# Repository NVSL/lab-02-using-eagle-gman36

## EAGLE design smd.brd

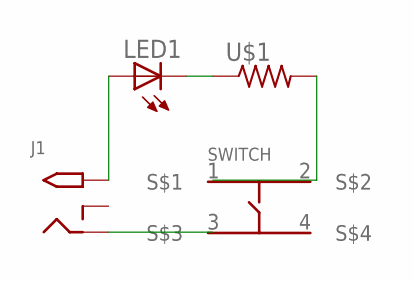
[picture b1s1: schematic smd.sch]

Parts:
J1: 2.1MMJACKTHM; PJ-102A
LED1: LED5MM
S1: 1301.9315
U$1: RESISTORTH-1/4W-CARBON; RESAD1160W55L680D260_HS

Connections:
unnamed: J1.TIP, LED1.A
unnamed: LED1.K (C), U$1.1

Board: 2 copper layers, 5 parts (0 on the bottom side), 2 nets, no tracks yet.

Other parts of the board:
U$3: UCSD_LOGO_LARGE

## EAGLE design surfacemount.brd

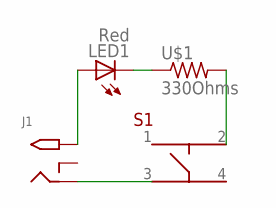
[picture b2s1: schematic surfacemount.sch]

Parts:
J1: 2.1MMJACKTHM; PJ-102A
LED1: Red; LED5MM
S1: 1301.9315
U$1: 330Ohms; RESAD1160W55L680D260_HS

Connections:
unnamed: J1.TIP, LED1.A
unnamed: LED1.K (C), U$1.1
unnamed: S1.2, U$1.2
unnamed: J1.RING, S1.3

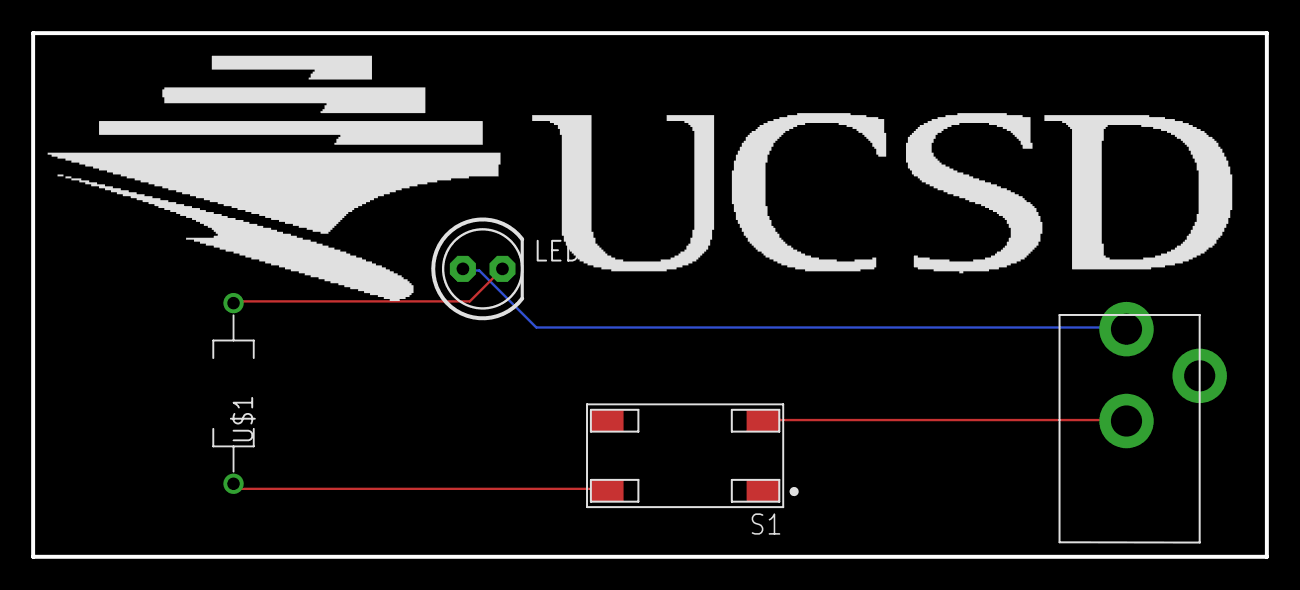
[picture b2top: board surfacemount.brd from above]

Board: 2 copper layers, 79.2 x 33.6 mm, 5 parts (0 on the bottom side), 4 nets.

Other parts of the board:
U$3: UCSD_LOGO_LARGE

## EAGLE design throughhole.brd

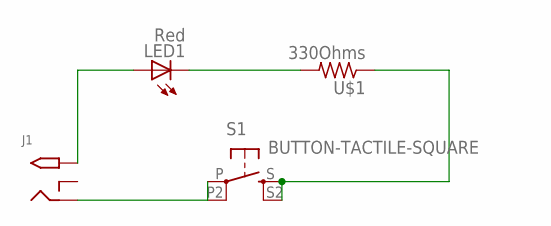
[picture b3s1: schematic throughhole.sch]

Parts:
J1: 2.1MMJACKTHM; PJ-102A
LED1: Red; LED5MM
S1: BUTTON-TACTILE-SQUARE; BUTTON-TACTILE-SQUARE-ADAFRUIT1010
U$1: 330Ohms; RESAD1160W55L680D260_HS

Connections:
unnamed: S1.S, S1.S2 (S1), U$1.1
unnamed: J1.RING, S1.P, S1.P2 (P1)
unnamed: J1.TIP, LED1.A
unnamed: LED1.K (C), U$1.2

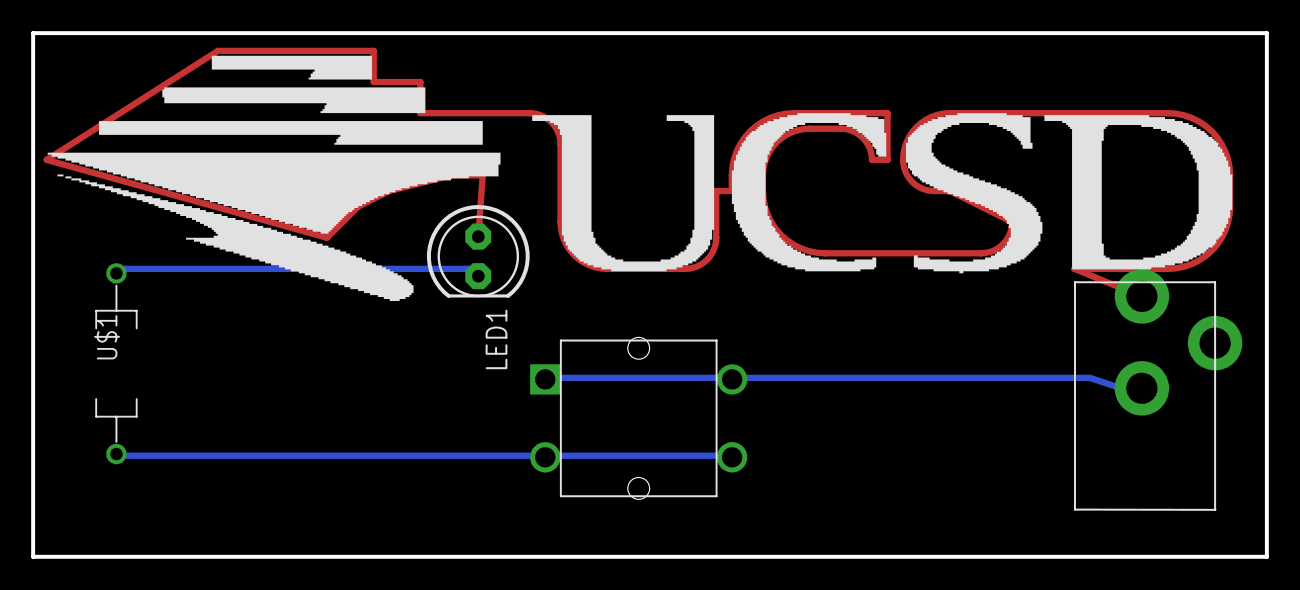
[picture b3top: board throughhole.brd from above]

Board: 2 copper layers, 79.2 x 33.6 mm, 5 parts (0 on the bottom side), 4 nets.

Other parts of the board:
U$3: UCSD_LOGO_LARGE

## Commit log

2016-04-07 Submission
2016-04-07 Added FreeDFM
2016-04-07 Fixed smd
2016-04-07 Re-Submission
